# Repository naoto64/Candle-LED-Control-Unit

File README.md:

# 1/fゆらぎLEDキャンドルキット
1/f ゆらぎのリアルな炎をマイコン制御で再現した LED キャンドルキットです。

[製品ページ](https://naoto64.github.io/Candle-LED-Control-Unit/ "1/fゆらぎLEDキャンドルキット 製品ページ")

[取扱説明書](https://naoto64.github.io/Candle-LED-Control-Unit/ "1/fゆらぎLEDキャンドルキット 取扱説明書")

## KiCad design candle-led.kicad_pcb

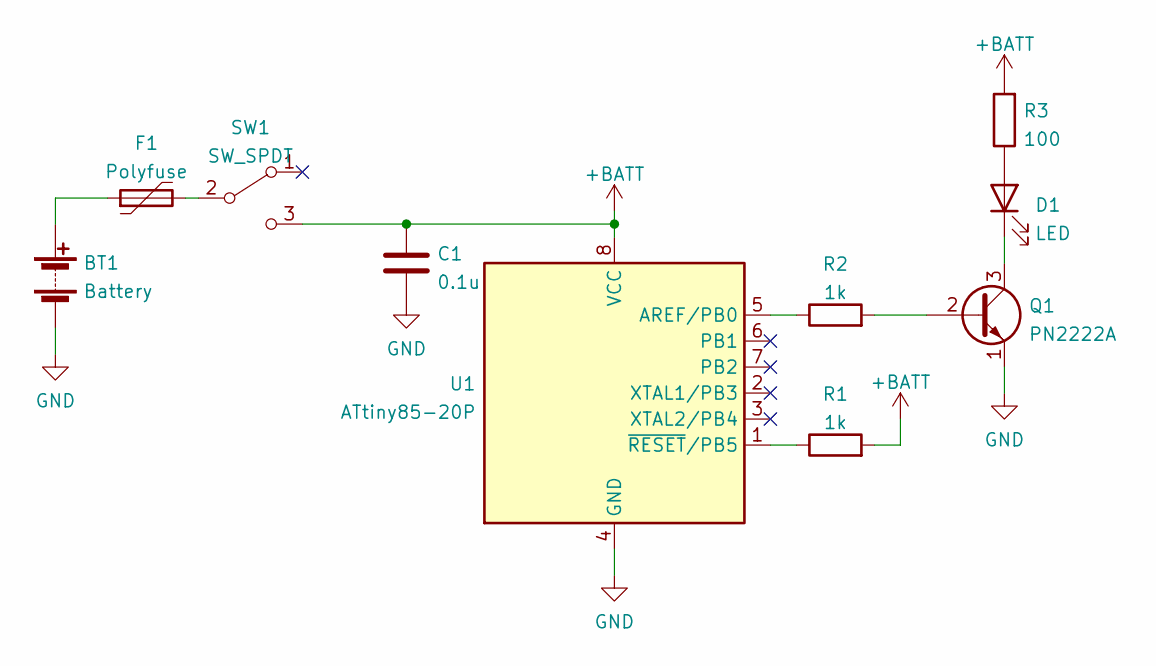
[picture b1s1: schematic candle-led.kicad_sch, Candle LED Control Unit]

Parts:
BT1: Battery; BatteryHolder_TruPower_BH-331P_3xAA
C1: 0.1u; C_Disc_D3.0mm_W1.6mm_P2.50mm
D1: LED; LED_D3.0mm
F1: Polyfuse; Fuse_Bourns_MF-RHT050
Q1: PN2222A; TO-92_Inline_Wide
R1, R2: 1k; R_Axial_DIN0204_L3.6mm_D1.6mm_P2.54mm_Vertical
R3: 100; R_Axial_DIN0204_L3.6mm_D1.6mm_P2.54mm_Vertical
SW1: SW_SPDT; PinHeader_1x03_P2.54mm_Vertical
U1: ATtiny85-20P; DIP-8_W7.62mm_Socket

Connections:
+BATT: C1.1, R1.2, R3.2, SW1.3 (C), U1.8 (VCC)
GND: BT1.2 (-), C1.2, Q1.1 (E), U1.4 (GND)
unnamed: BT1.1 (+), F1.1
unnamed: D1.1 (K), Q1.3 (C)
unnamed: D1.2 (A), R3.1
unnamed: F1.2, SW1.2 (B)
unnamed: Q1.2 (B), R2.2
unnamed: R1.1, U1.1 (~RESET/PB5)
unnamed: R2.1, U1.5 (AREF/PB0)

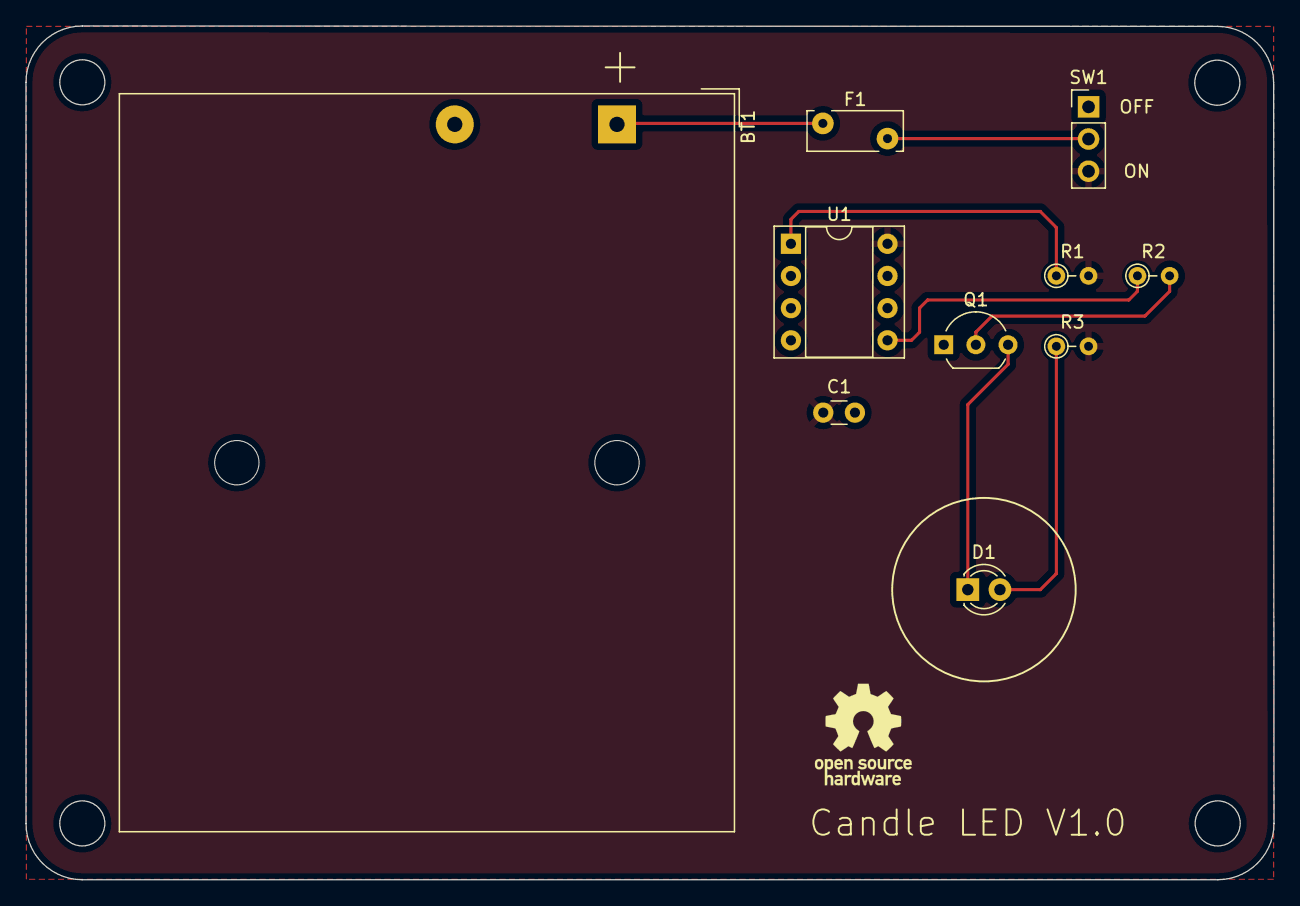
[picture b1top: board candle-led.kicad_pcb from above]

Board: 2 copper layers, 98.5 x 67.4 mm, 10 parts (0 on the bottom side), 9 nets.
